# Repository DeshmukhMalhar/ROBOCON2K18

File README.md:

# ROBOCON2K18

repo for all the technical data generated by us for robocon 2018

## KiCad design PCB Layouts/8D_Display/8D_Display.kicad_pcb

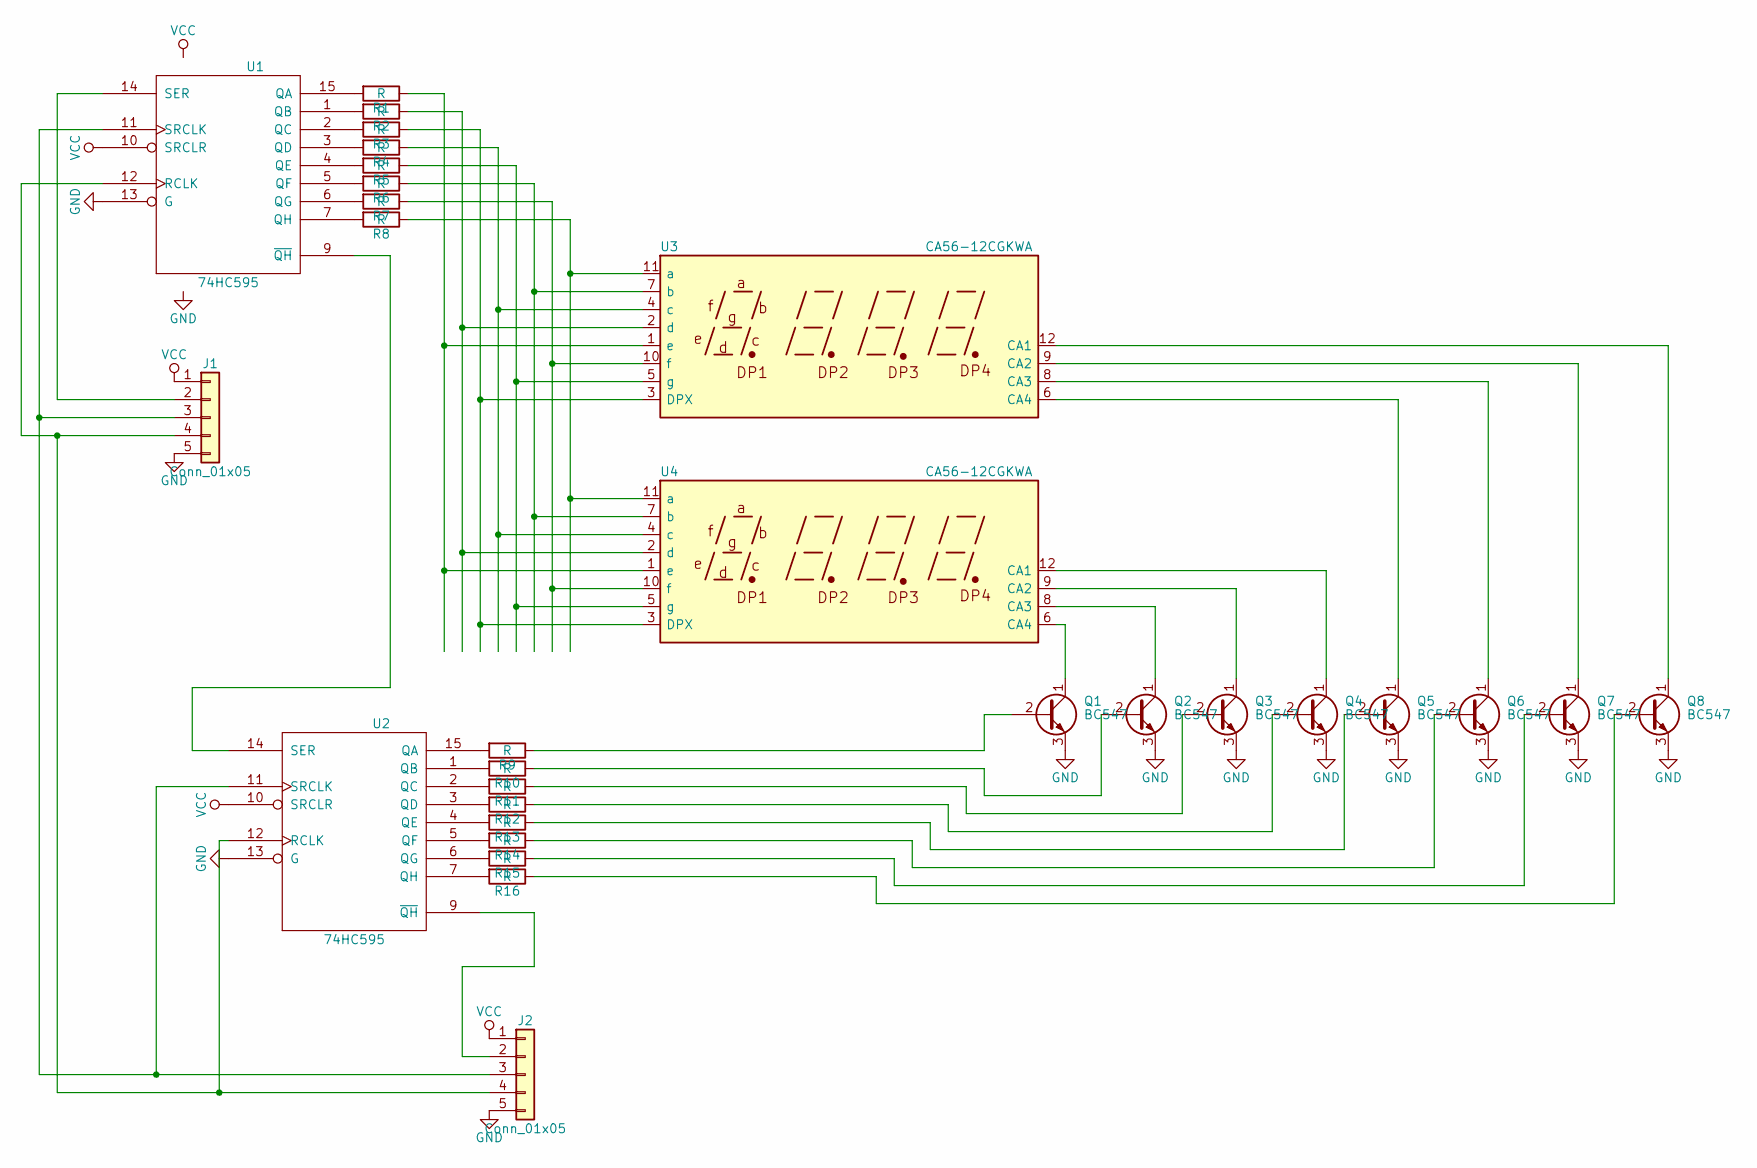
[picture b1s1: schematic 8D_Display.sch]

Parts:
J1, J2: Conn_01x05; Pin_Header_Straight_1x05_Pitch2.54mm
Q1, Q2, Q3, Q4, Q5, Q6, Q7, Q8: BC547; TO-92_Molded_Narrow
R1, R2, R3, R4, R5, R6, R7, R8, R9, R10, R11, R12, R13, R14, R15, R16: R; R_Axial_DIN0207_L6.3mm_D2.5mm_P5.08mm_Vertical
U1, U2: 74HC595; DIP-16_W7.62mm_LongPads
U3, U4: CA56-12CGKWA

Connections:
GND: J1.5, J2.5, Q1.3 (E), Q2.3 (E), Q3.3 (E), Q4.3 (E), Q5.3 (E), Q6.3 (E), Q7.3 (E), Q8.3 (E), U1.8 (GND), U1.13 (G), U2.8 (GND), U2.13 (G)
unnamed: J1.2, U1.14 (SER)
unnamed: J1.3, J2.3, U1.11 (SRCLK), U2.11 (SRCLK)
unnamed: J1.4, J2.4, U1.12 (RCLK), U2.12 (RCLK)
unnamed: J2.2, U2.9 (~QH)
unnamed: Q1.1 (C), U4.6 (CA4)
unnamed: Q1.2 (B), R9.1
unnamed: Q2.1 (C), U4.8 (CA3)
unnamed: Q2.2 (B), R10.1
unnamed: Q3.1 (C), U4.9 (CA2)
unnamed: Q3.2 (B), R11.1
unnamed: Q4.1 (C), U4.12 (CA1)
unnamed: Q4.2 (B), R12.1
unnamed: Q5.1 (C), U3.6 (CA4)
unnamed: Q5.2 (B), R13.1
unnamed: Q6.1 (C), U3.8 (CA3)
unnamed: Q6.2 (B), R14.1
unnamed: Q7.1 (C), U3.9 (CA2)
unnamed: Q7.2 (B), R15.1
unnamed: Q8.1 (C), U3.12 (CA1)
unnamed: Q8.2 (B), R16.1
unnamed: R1.1, U3.1 (e), U4.1 (e)
unnamed: R1.2, U1.15 (QA)
unnamed: R2.1, U3.2 (d), U4.2 (d)
unnamed: R2.2, U1.1 (QB)
unnamed: R3.1, U3.3 (DPX), U4.3 (DPX)
unnamed: R3.2, U1.2 (QC)
unnamed: R4.1, U3.4 (c), U4.4 (c)
unnamed: R4.2, U1.3 (QD)
unnamed: R5.1, U3.5 (g), U4.5 (g)
unnamed: R5.2, U1.4 (QE)
unnamed: R6.1, U3.7 (b), U4.7 (b)
unnamed: R6.2, U1.5 (QF)
unnamed: R7.1, U3.10 (f), U4.10 (f)
unnamed: R7.2, U1.6 (QG)
unnamed: R8.1, U3.11 (a), U4.11 (a)
unnamed: R8.2, U1.7 (QH)
unnamed: R9.2, U2.15 (QA)
unnamed: R10.2, U2.1 (QB)
unnamed: R11.2, U2.2 (QC)
unnamed: R12.2, U2.3 (QD)
unnamed: R13.2, U2.4 (QE)
unnamed: R14.2, U2.5 (QF)
unnamed: R15.2, U2.6 (QG)
unnamed: R16.2, U2.7 (QH)
unnamed: U1.9 (~QH), U2.14 (SER)
VCC: J1.1, J2.1, U1.10 (SRCLR), U1.16 (VCC), U2.10 (SRCLR), U2.16 (VCC)

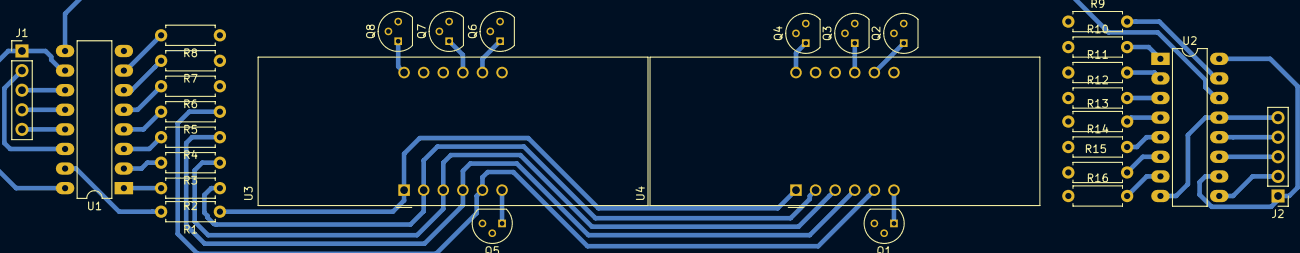
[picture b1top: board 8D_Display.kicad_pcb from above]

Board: 2 copper layers, 30 parts (0 on the bottom side), 47 nets.

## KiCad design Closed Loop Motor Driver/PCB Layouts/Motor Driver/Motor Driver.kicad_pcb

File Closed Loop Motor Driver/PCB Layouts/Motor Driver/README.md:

__Motor Driver__

This Board receives a pulse like input, similat to a Servo.
The input range is from 0 degrees to 90 degrees for one direction
and 90 to 180 degrees for other direction 
The Board is still under devlopement.
It will be optimised for single sided PCB as to simplify etching and testing at home

A full closed loop RPM control system will be devloped for this

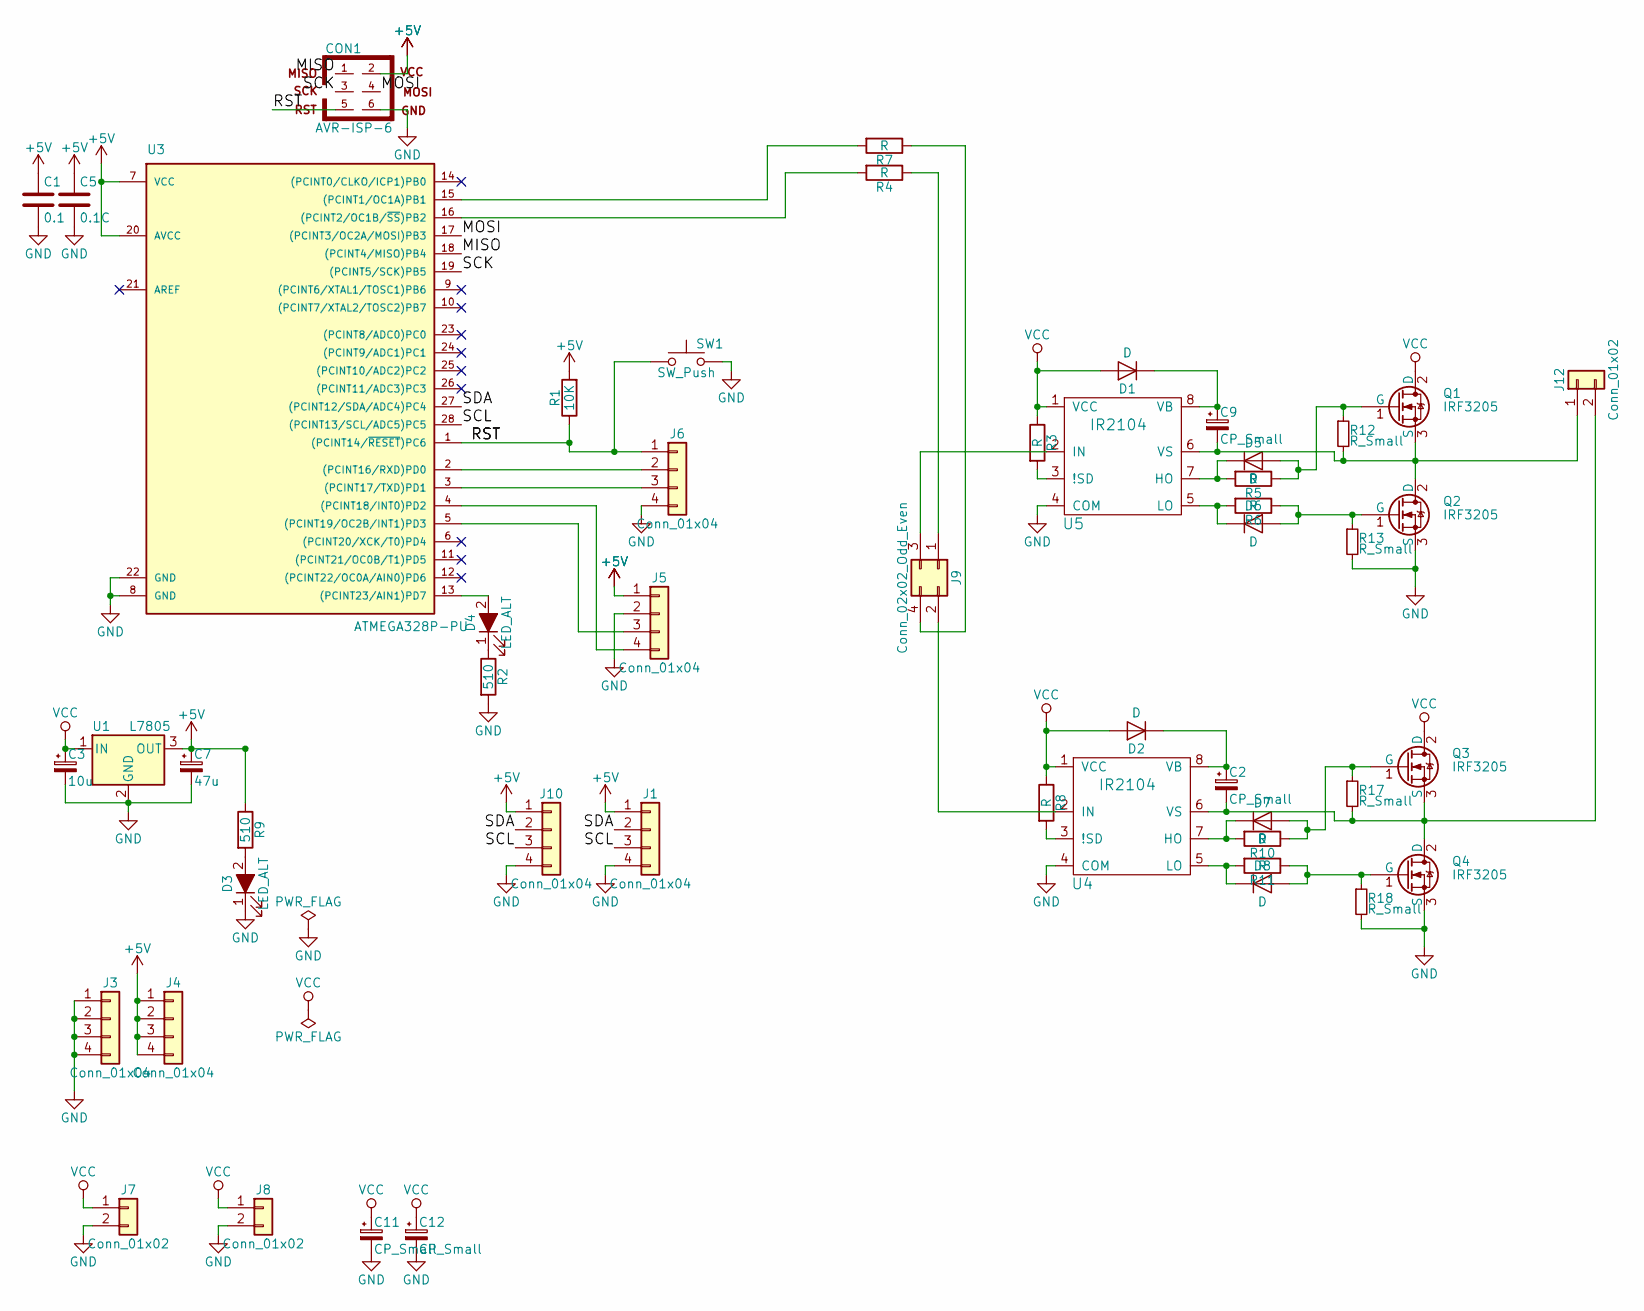
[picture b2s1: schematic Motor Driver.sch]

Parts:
C1: 0.1; C_Disc_D3.0mm_W2.0mm_P2.50mm
C2, C9: CP_Small; CP_Radial_D5.0mm_P2.00mm
C3: 10u; CP_Radial_D10.0mm_P2.50mm_P5.00mm
C5: 0.1C; C_Disc_D3.0mm_W2.0mm_P2.50mm
C7: 47u; CP_Radial_D6.3mm_P2.50mm
C11, C12: CP_Small; CP_Radial_D10.0mm_P2.50mm_P5.00mm
CON1: AVR-ISP-6; Pin_Header_Straight_2x03_Pitch2.54mm
D1, D2, D5, D6, D7, D8: D; D_A-405_P7.62mm_Horizontal
D3, D4: LED_ALT; LED_D5.0mm
J1, J3, J4, J6, J10: Conn_01x04; Pin_Header_Straight_1x04_Pitch2.54mm
J5: Conn_01x04; JST_PH_B4B-PH-K_04x2.00mm_Straight
J7, J8: Conn_01x02; WAGO_734_2pin_Straight_RuggedPads
J9: Conn_02x02_Odd_Even; Pin_Header_Straight_2x02_Pitch2.54mm
J12: Conn_01x02; Hirose_DF63-2P-3.96DSA_02x3.96mm_Straight
Q1, Q2, Q3, Q4: IRF3205; TO-220-3_Vertical
R1: 10K; R_Axial_DIN0207_L6.3mm_D2.5mm_P7.62mm_Horizontal
R2, R9: 510; R_Axial_DIN0207_L6.3mm_D2.5mm_P7.62mm_Horizontal
R3, R4, R5, R6, R7, R8, R10, R11: R; R_Axial_DIN0207_L6.3mm_D2.5mm_P7.62mm_Horizontal
R12, R13, R17, R18: R_Small; R_Axial_DIN0207_L6.3mm_D2.5mm_P7.62mm_Horizontal
SW1: SW_Push; SW_TH_Tactile_Omron_B3F-10xx
U1: L7805; TO-220-3_Vertical
U3: ATMEGA328P-PU; DIP-28_W7.62mm_Socket_LongPads
U4, U5: IR2104; DIP-8_W7.62mm_Socket_LongPads

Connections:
+5V: C1.1, C5.1, C7.1, CON1.2, J1.1, J4.1, J4.2, J4.3, J4.4, J5.1, J10.1, R1.2, R9.1, U1.3 (OUT), U3.7 (VCC), U3.20 (AVCC)
/MISO: CON1.1, U3.18 ((PCINT4/MISO)PB4)
/MOSI: CON1.4, U3.17 ((PCINT3/OC2A/MOSI)PB3)
/RST: CON1.5, J6.1, R1.1, SW1.1, SW1.3, U3.1 ((PCINT14/~RESET~)PC6)
/SCK: CON1.3, U3.19 ((PCINT5/SCK)PB5)
/SCL: J1.3, J10.3, U3.28 ((PCINT13/SCL/ADC5)PC5)
/SDA: J1.2, J10.2, U3.27 ((PCINT12/SDA/ADC4)PC4)
GND: C1.2, C3.2, C5.2, C7.2, C11.2, C12.2, CON1.6, D3.1 (K), J1.4, J3.1, J3.2, J3.3, J3.4, J5.2, J6.4, J7.2, J8.2, J10.4, Q2.3 (S), Q4.3 (S), R2.2, R13.2, R18.2, SW1.2, SW1.4, U1.2 (GND), U3.8 (GND), U3.22 (GND), U4.4 (COM), U5.4 (COM)
unnamed: C2.1, D2.1 (K), U4.8 (VB)
unnamed: C2.2, J12.2, Q3.3 (S), Q4.2 (D), R17.2, U4.6 (VS)
unnamed: C9.1, D1.1 (K), U5.8 (VB)
unnamed: C9.2, J12.1, Q1.3 (S), Q2.2 (D), R12.2, U5.6 (VS)
unnamed: D3.2 (A), R9.2
unnamed: D4.1 (K), R2.1
unnamed: D4.2 (A), U3.13 ((PCINT23/AIN1)PD7)
unnamed: D5.1 (K), R5.2, U5.7 (HO)
unnamed: D5.2 (A), Q1.1 (G), R5.1, R12.1
unnamed: D6.1 (K), R6.2, U5.5 (LO)
unnamed: D6.2 (A), Q2.1 (G), R6.1, R13.1
unnamed: D7.1 (K), R10.2, U4.7 (HO)
unnamed: D7.2 (A), Q3.1 (G), R10.1, R17.1
unnamed: D8.1 (K), R11.2, U4.5 (LO)
unnamed: D8.2 (A), Q4.1 (G), R11.1, R18.1
unnamed: J5.3, U3.5 ((PCINT19/OC2B/INT1)PD3)
unnamed: J5.4, U3.4 ((PCINT18/INT0)PD2)
unnamed: J6.2, U3.2 ((PCINT16/RXD)PD0)
unnamed: J6.3, U3.3 ((PCINT17/TXD)PD1)
unnamed: J9.1, R4.1
unnamed: J9.2, U4.2 (IN)
unnamed: J9.3, U5.2 (IN)
unnamed: J9.4, R7.1
unnamed: R3.2, U5.3 (!SD)
unnamed: R4.2, U3.16 ((PCINT2/OC1B/~SS~)PB2)
unnamed: R7.2, U3.15 ((PCINT1/OC1A)PB1)
unnamed: R8.2, U4.3 (!SD)
VCC: C3.1, C11.1, C12.1, D1.2 (A), D2.2 (A), J7.1, J8.1, Q1.2 (D), Q3.2 (D), R3.1, R8.1, U1.1 (IN), U4.1 (VCC), U5.1 (VCC)

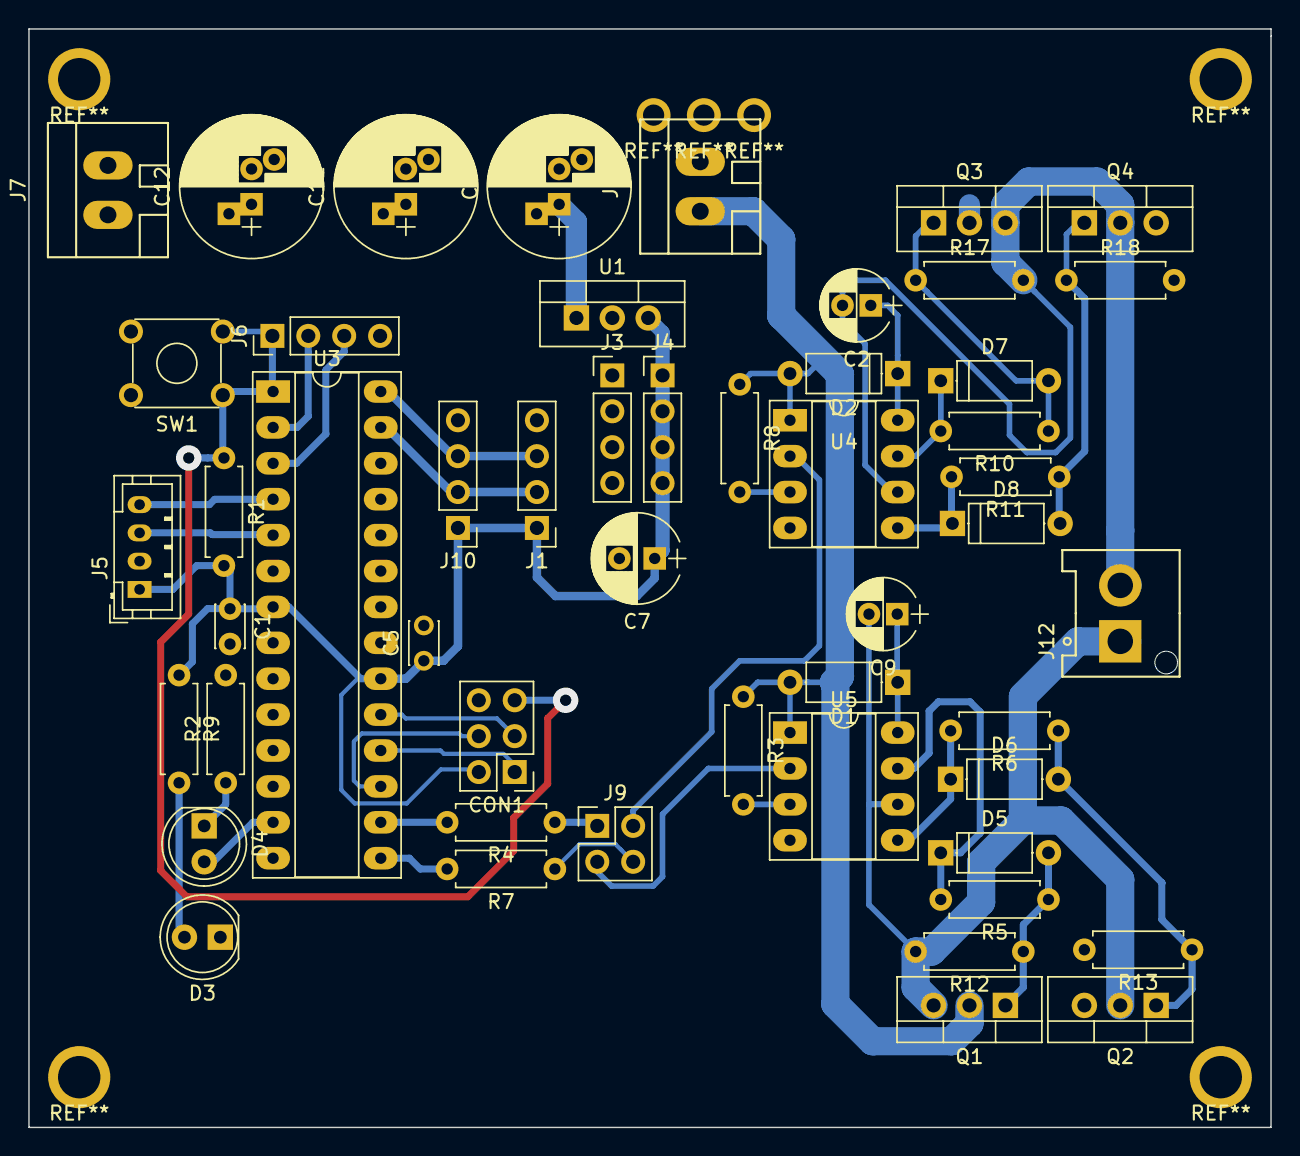
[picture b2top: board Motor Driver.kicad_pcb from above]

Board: 2 copper layers, 87.9 x 77.7 mm, 51 parts (0 on the bottom side), 36 nets.

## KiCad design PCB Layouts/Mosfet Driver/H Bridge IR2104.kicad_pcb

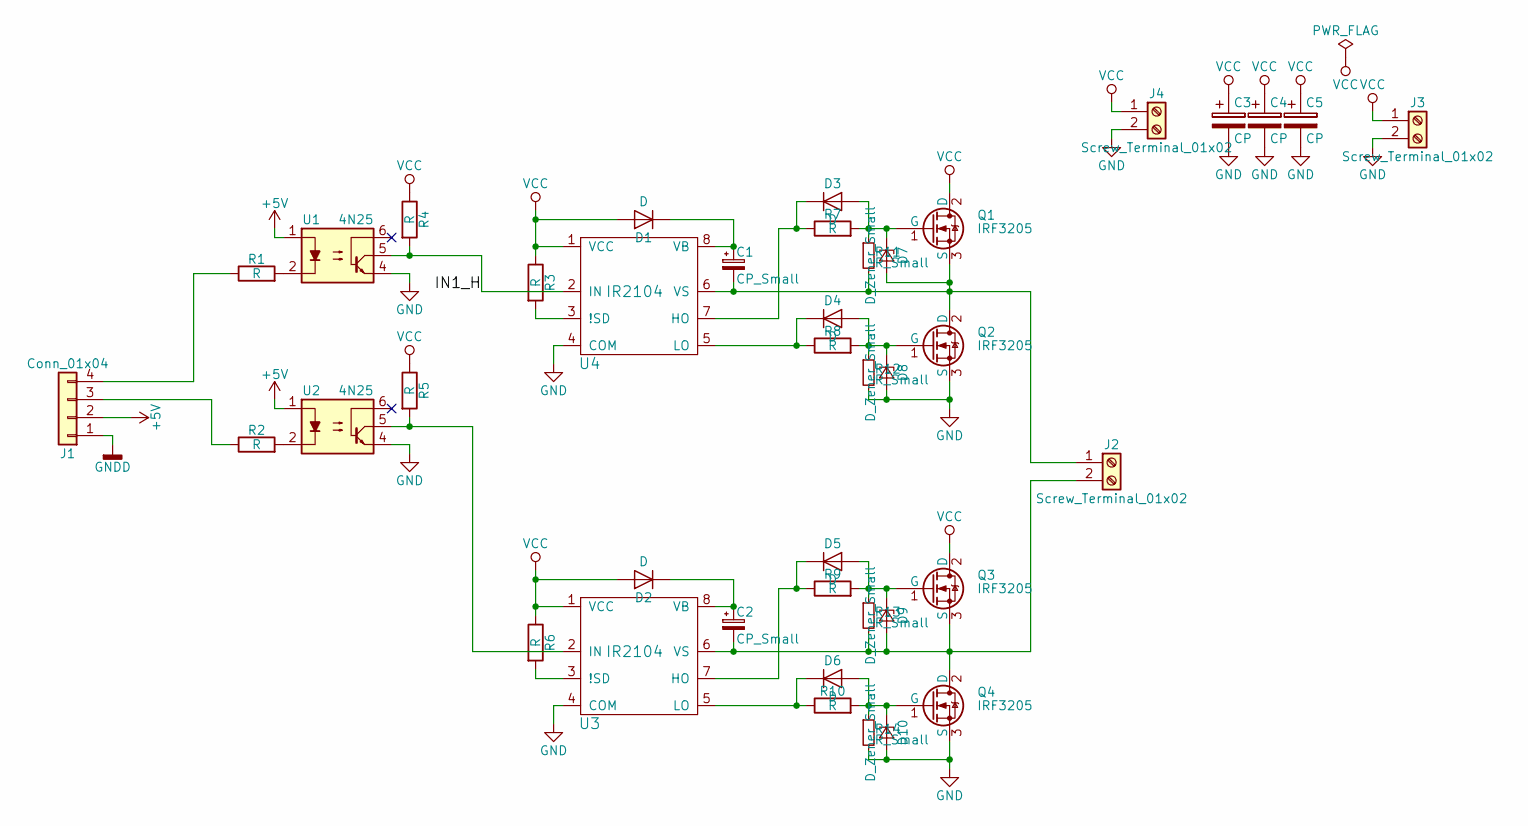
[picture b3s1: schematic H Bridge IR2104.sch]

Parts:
C1, C2: CP_Small; CP_Radial_D5.0mm_P2.50mm
C3, C4, C5: CP; CP_Radial_D10.0mm_P2.50mm_P5.00mm
D1, D2, D3, D4, D5, D6: D; D_A-405_P7.62mm_Horizontal
D7, D8, D9, D10: D_Zener_Small; D_A-405_P7.62mm_Horizontal
J1: Conn_01x04; Pin_Header_Straight_1x04_Pitch2.54mm
J2, J3, J4: Screw_Terminal_01x02; WAGO_734_2pin_Straight
Q1, Q2, Q3, Q4: IRF3205; TO-220-3_Vertical
R1, R2, R3, R4, R5, R6, R7, R8, R9, R10: R; R_Axial_DIN0207_L6.3mm_D2.5mm_P7.62mm_Horizontal
R11, R12, R13, R14: R_Small; R_Axial_DIN0207_L6.3mm_D2.5mm_P7.62mm_Horizontal
U1, U2: 4N25; DIP-6_W7.62mm
U3, U4: IR2104; DIP-8_W7.62mm_LongPads

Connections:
+5V: J1.2, U1.1, U2.1
/IN1_H: R4.2, U1.5, U4.2 (IN)
GND: C3.2, C4.2, C5.2, D8.2 (A), D10.2 (A), J3.2, J4.2, Q2.3 (S), Q4.3 (S), R12.2, R14.2, U1.4, U2.4, U3.4 (COM), U4.4 (COM)
GNDD: J1.1
unnamed: C1.1, D1.1 (K), U4.8 (VB)
unnamed: C1.2, D7.2 (A), J2.1, Q1.3 (S), Q2.2 (D), R11.2, U4.6 (VS)
unnamed: C2.1, D2.1 (K), U3.8 (VB)
unnamed: C2.2, D9.2 (A), J2.2, Q3.3 (S), Q4.2 (D), R13.2, U3.6 (VS)
unnamed: D3.1 (K), R7.1, U4.7 (HO)
unnamed: D3.2 (A), D7.1 (K), Q1.1 (G), R7.2, R11.1
unnamed: D4.1 (K), R8.1, U4.5 (LO)
unnamed: D4.2 (A), D8.1 (K), Q2.1 (G), R8.2, R12.1
unnamed: D5.1 (K), R9.1, U3.7 (HO)
unnamed: D5.2 (A), D9.1 (K), Q3.1 (G), R9.2, R13.1
unnamed: D6.1 (K), R10.1, U3.5 (LO)
unnamed: D6.2 (A), D10.1 (K), Q4.1 (G), R10.2, R14.1
unnamed: J1.3, R2.1
unnamed: J1.4, R1.1
unnamed: R1.2, U1.2
unnamed: R2.2, U2.2
unnamed: R3.2, U4.3 (!SD)
unnamed: R5.2, U2.5, U3.2 (IN)
unnamed: R6.2, U3.3 (!SD)
VCC: C3.1, C4.1, C5.1, D1.2 (A), D2.2 (A), J3.1, J4.1, Q1.2 (D), Q3.2 (D), R3.1, R4.1, R5.1, R6.1, U3.1 (VCC), U4.1 (VCC)

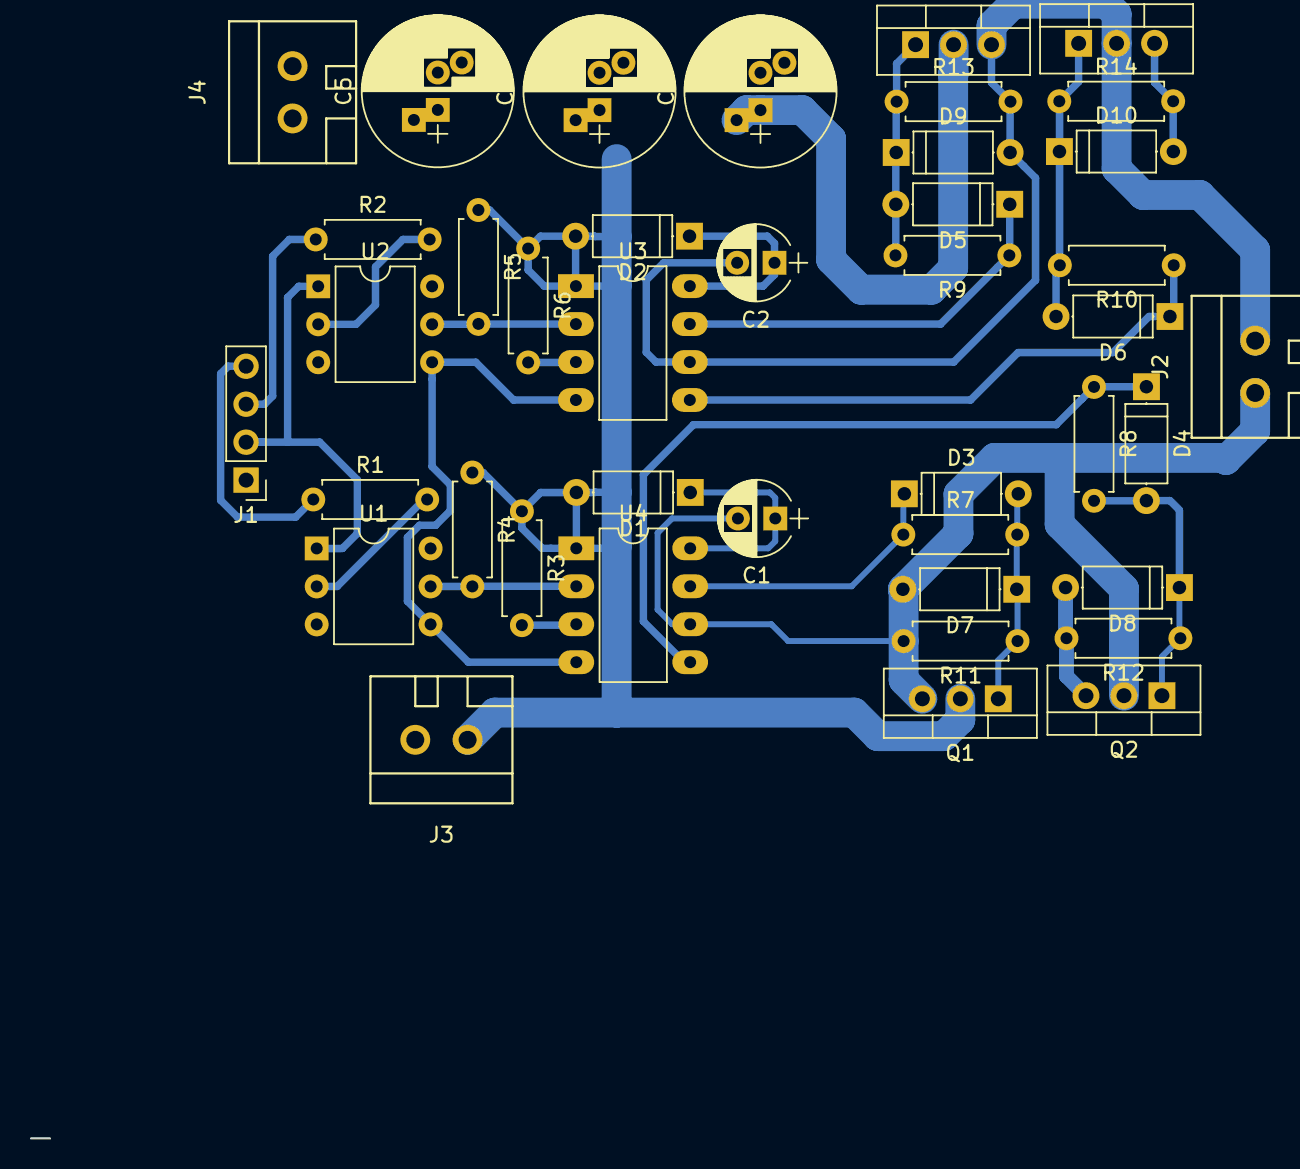
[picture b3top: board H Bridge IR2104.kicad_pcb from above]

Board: 2 copper layers, 41 parts (0 on the bottom side), 23 nets.

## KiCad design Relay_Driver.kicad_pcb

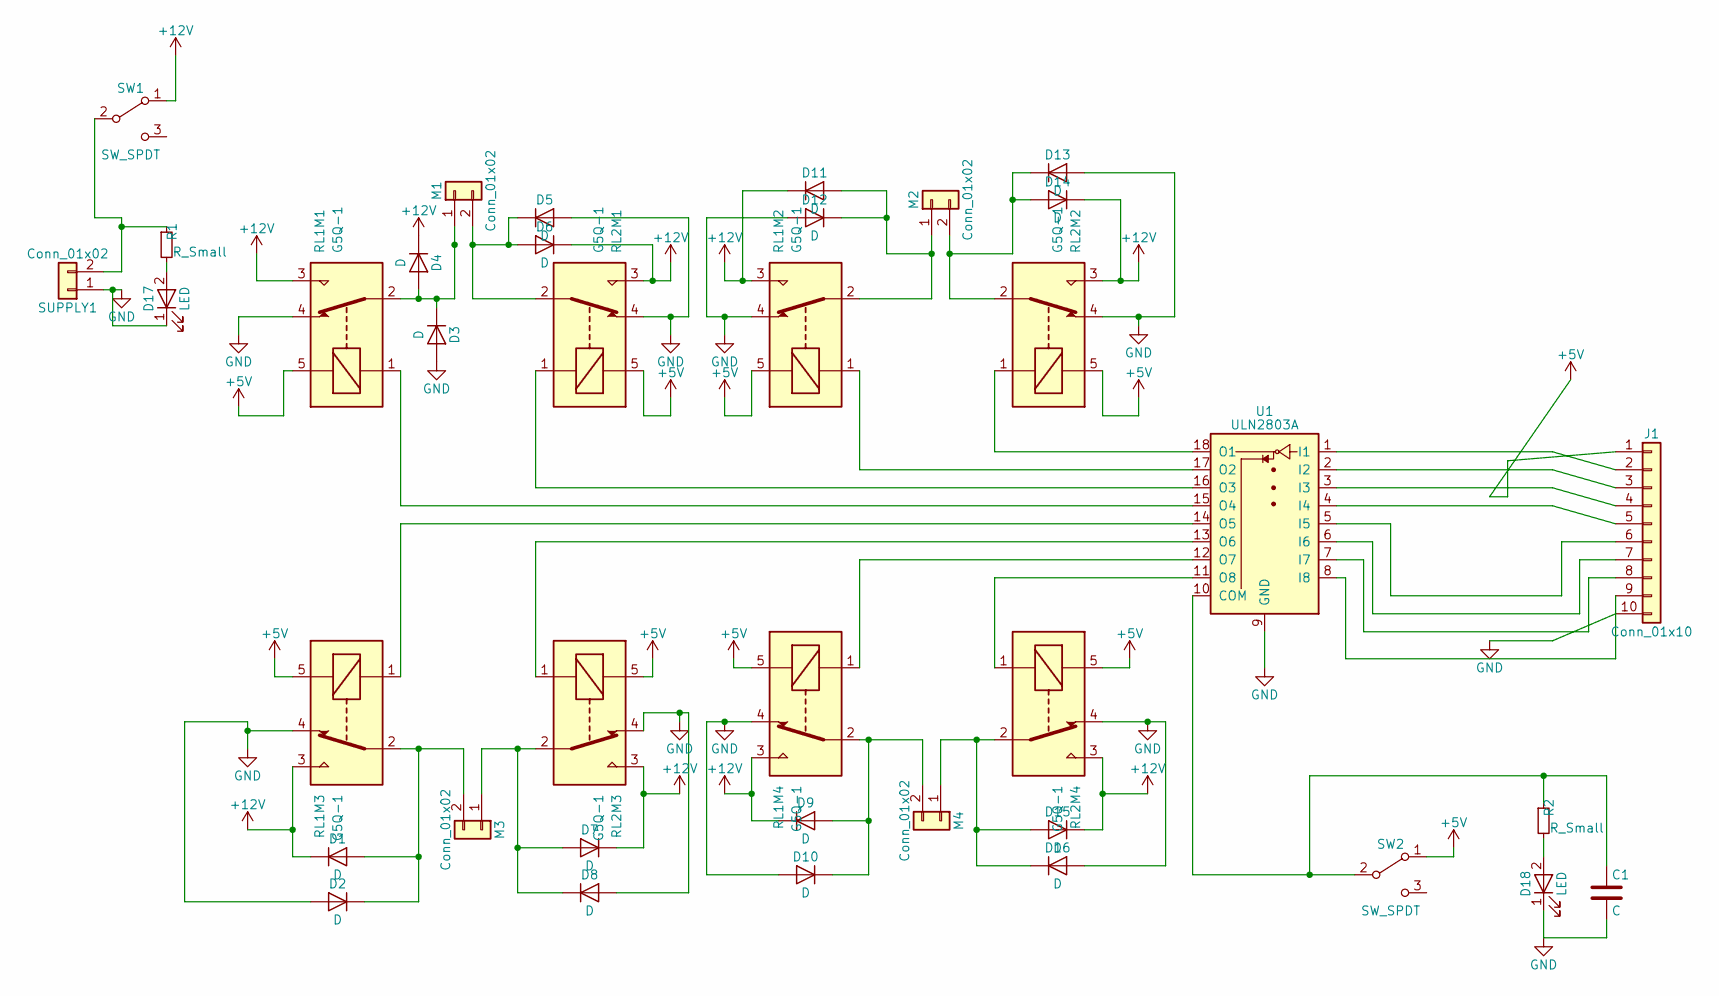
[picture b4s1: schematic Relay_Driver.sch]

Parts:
C1: C; C_Disc_D5.0mm_W2.5mm_P2.50mm
D1, D2, D3, D4, D5, D6, D7, D8, D9, D10, D11, D12, D13, D14, D15, D16: D; D_DO-15_P12.70mm_Horizontal
D17, D18: LED; LED_D5.0mm_FlatTop
J1: Conn_01x10; Pin_Header_Straight_1x10_Pitch1.00mm
M1, M2, M3, M4: Conn_01x02; WAGO_734_2pin_Straight_RuggedPads
R1, R2: R_Small; R_Axial_DIN0207_L6.3mm_D2.5mm_P7.62mm_Horizontal
RL1M1, RL1M2, RL1M3, RL1M4, RL2M1, RL2M2, RL2M3, RL2M4: G5Q-1; Relay_SPDT_OMRON-G5LE-1
SUPPLY1: Conn_01x02; WAGO_734_2pin_Straight_RuggedPads
SW1, SW2: SW_SPDT; SW_CuK_OS102011MA1QN1_SPDT_Angled
U1: ULN2803A; DIP-18_W7.62mm_LongPads

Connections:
+5V: J1.1, RL1M1.5, RL1M2.5, RL1M3.5, RL1M4.5, RL2M1.5, RL2M2.5, RL2M3.5, RL2M4.5, SW2.1 (A)
+12V: D1.1 (K), D4.1 (K), D6.1 (K), D7.1 (K), D9.1 (K), D11.1 (K), D14.1 (K), D15.1 (K), RL1M1.3, RL1M2.3, RL1M3.3, RL1M4.3, RL2M1.3, RL2M2.3, RL2M3.3, RL2M4.3, SW1.1 (A)
GND: C1.2, D2.2 (A), D3.2 (A), D5.2 (A), D8.2 (A), D10.2 (A), D12.2 (A), D13.2 (A), D16.2 (A), D17.1 (K), D18.1 (K), J1.10, RL1M1.4, RL1M2.4, RL1M3.4, RL1M4.4, RL2M1.4, RL2M2.4, RL2M3.4, RL2M4.4, SUPPLY1.1, U1.9 (GND)
unnamed: C1.1, R2.1, SW2.2 (B), U1.10 (COM)
unnamed: D1.2 (A), D2.1 (K), M3.2, RL1M3.2
unnamed: D3.1 (K), D4.2 (A), M1.1, RL1M1.2
unnamed: D5.1 (K), D6.2 (A), M1.2, RL2M1.2
unnamed: D7.2 (A), D8.1 (K), M3.1, RL2M3.2
unnamed: D9.2 (A), D10.1 (K), M4.2, RL1M4.2
unnamed: D11.2 (A), D12.1 (K), M2.1, RL1M2.2
unnamed: D13.1 (K), D14.2 (A), M2.2, RL2M2.2
unnamed: D15.2 (A), D16.1 (K), M4.1, RL2M4.2
unnamed: D17.2 (A), R1.2
unnamed: D18.2 (A), R2.2
unnamed: J1.2, U1.1 (I1)
unnamed: J1.3, U1.2 (I2)
unnamed: J1.4, U1.3 (I3)
unnamed: J1.5, U1.4 (I4)
unnamed: J1.6, U1.5 (I5)
unnamed: J1.7, U1.6 (I6)
unnamed: J1.8, U1.7 (I7)
unnamed: J1.9, U1.8 (I8)
unnamed: R1.1, SUPPLY1.2, SW1.2 (B)
unnamed: RL1M1.1, U1.15 (O4)
unnamed: RL1M2.1, U1.17 (O2)
unnamed: RL1M3.1, U1.14 (O5)
unnamed: RL1M4.1, U1.12 (O7)
unnamed: RL2M1.1, U1.16 (O3)
unnamed: RL2M2.1, U1.18 (O1)
unnamed: RL2M3.1, U1.13 (O6)
unnamed: RL2M4.1, U1.11 (O8)

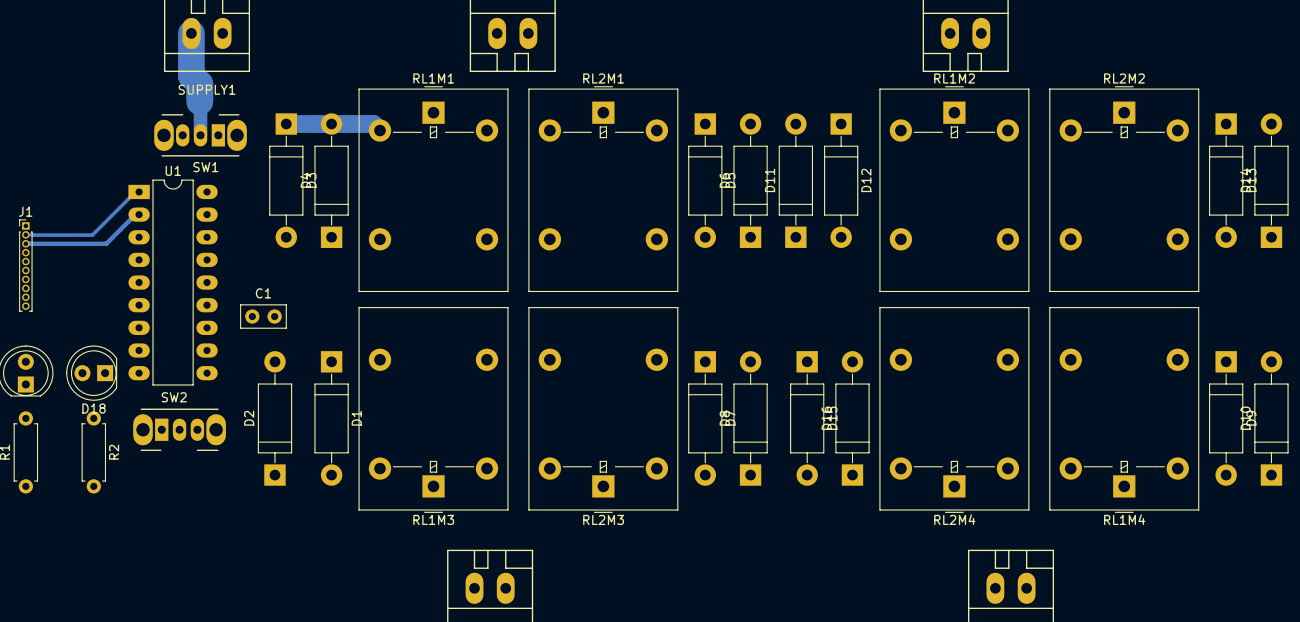
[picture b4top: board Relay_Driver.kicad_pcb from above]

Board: 2 copper layers, 38 parts (0 on the bottom side), 31 nets.

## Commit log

2017-12-18 moved files into folder
2017-12-29 Aded codes for testing new motor
2017-12-30 Reorganised the folder stracture
2017-12-30 Added PCB files for MOSFET DRIVER
2018-01-08 created repo for cytron codes
2018-01-09 added both codes primitive and optimized
2018-01-11 added folder stracture for new wireless controller
2018-01-14 schematics and board layout added.
    aeKUTuvug55
2018-01-14 Added basic sketch for closed loop controller
2018-01-14 Added the PCB layout for PID controller
2018-01-15 Modified the PID controller sketch for new Board
2018-01-16 Changed Tuning Parameters in PID controller
2018-01-19 Added new Cytron code
2018-01-20 Added I2C recv to PID controller. Added libraries
2018-01-20 Organized omni_cytron_test folder
2018-01-20 Removed serial prints
2018-01-20 Optimized
2018-01-21 Optimised
2018-01-21 Added description for code in Closed LOOP Motor Driver
2018-01-21 Added a critical assignment in PID controller sketch
2018-01-21 Added 8 digit display to repo
2018-01-23 Added 'I2c_anything' modified sketches
2018-01-24 Added library for Motor driver
2018-01-27 created folder Magnetometer and added code
2018-01-30 added code for cytron T config along with magnetometer
2018-01-30 Small changes and added gitignore
2018-02-01 made some minor changes
2018-02-02 some changes
2018-02-02 testing
2018-02-06 Final Code
2018-02-07 added motordriver library
2018-02-08 Changed a wrong fuse setting in AVRDUDE commands
2018-02-08 Modified IIC devlopement sketches in closed loop driver
2018-02-10 New updated code
2018-02-10 Optimised dynamic memory and time
2018-02-11 Started cleaning up arduino sketches
2018-02-12 changed pwm values for auto bot
2018-02-15 Added code for improved pinging
2018-02-15 enhanced code
2018-02-17 added code for proximity sensor
2018-02-18 enhanced traversal and added code for shuttlecock detection
2018-02-19 added Hardware definations for Wireless controller
2018-02-20 minor changes
2018-02-21 tuned for new bot
2018-02-23 added code for neopixel
2018-02-23 added code for pneumatic relay
2018-02-24 added code for daughter board
2018-02-25 added code for new motherboard and daughterboard
2018-02-25 code almost to be discarded communication 6 pins vaalaa
2018-02-25 almost final auto bot code
2018-02-27 minor additions
2018-02-27 just for self confirmation
